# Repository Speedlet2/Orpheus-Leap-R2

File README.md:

# Orpheus-Leap-R2

This is the repository containing the current basic ideas for [Hack Club's](https://github.com/hackclub) new 'Orpheus Leap' uController board. The original version was designed by [Kevin Yang](https://github.com/kvnyng) in 2020 and can be found [here](https://github.com/kvnyng/Orpheus-Leap-Micro). This is currently very early in development, with the basic architecture not yet finalised. Feel free to add any ideas/problems in an issue

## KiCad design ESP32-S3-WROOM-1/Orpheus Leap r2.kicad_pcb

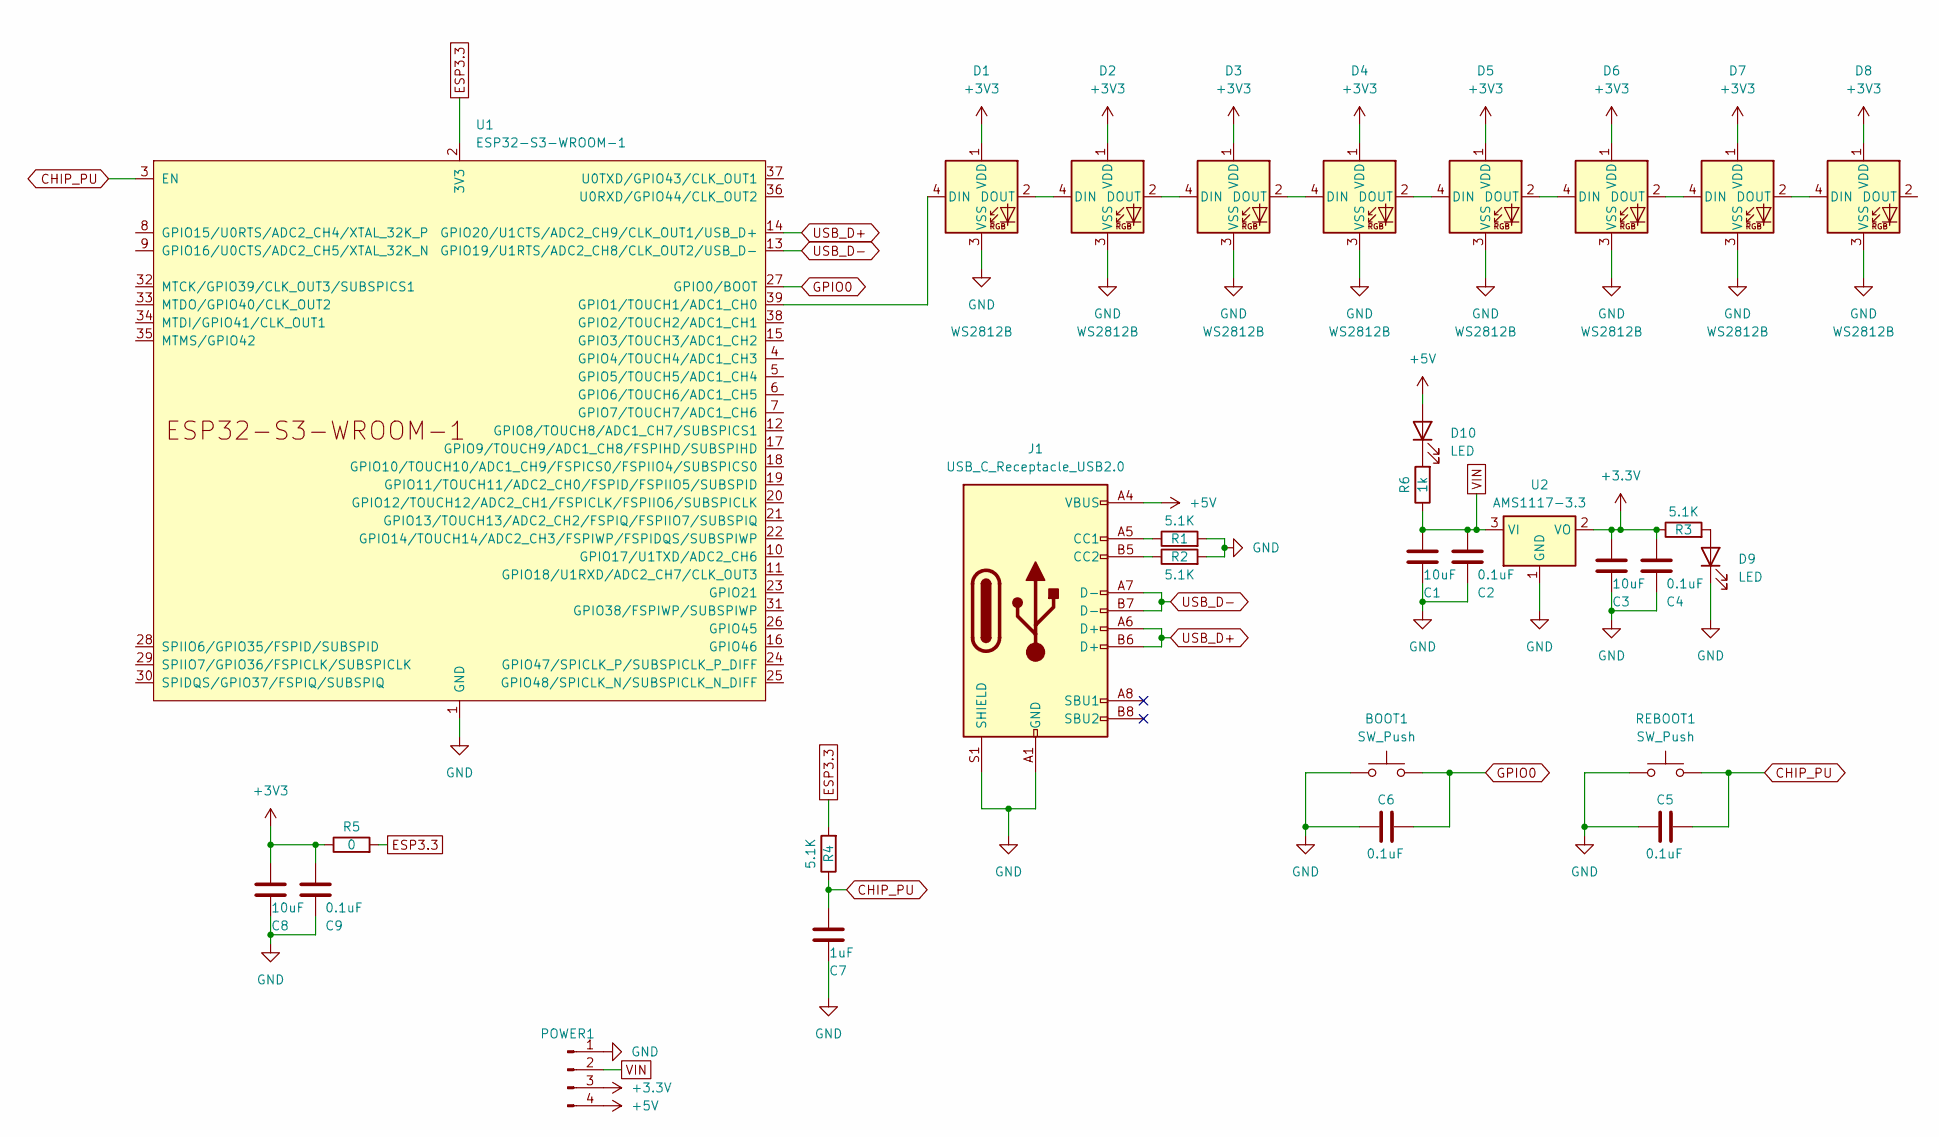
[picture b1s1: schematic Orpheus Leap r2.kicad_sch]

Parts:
BOOT1: SW_Push; SW_PUSH_6mm
C1, C3, C8: 10uF; C_0603_1608Metric
C2, C4, C5, C6, C9: 0.1uF; C_0603_1608Metric
C7: 1uF; C_0603_1608Metric
D1, D2, D3, D4, D5, D6, D7, D8: WS2812B; LED_WS2812B_PLCC4_5.0x5.0mm_P3.2mm
D9, D10: LED; LED_D3.0mm
J1: USB_C_Receptacle_USB2.0; USB_C_Receptacle_JAE_DX07S016JA1R1500
POWER1: Conn_01x04_Pin; PinHeader_1x04_P2.54mm_Vertical
R1, R2, R3, R4: 5.1K; R_0201_0603Metric
R5: 0; R_0201_0603Metric
R6: 1k; R_0201_0603Metric
REBOOT1: SW_Push; SW_PUSH_6mm
U1: ESP32-S3-WROOM-1
U2: AMS1117-3.3; SOT-223-3_TabPin2

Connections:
+3.3V: C3.1, C4.1, POWER1.3, R3.1, U2.2 (VO)
+3V3: C8.1, C9.1, D1.1 (VDD), D2.1 (VDD), D3.1 (VDD), D4.1 (VDD), D5.1 (VDD), D6.1 (VDD), D7.1 (VDD), D8.1 (VDD), R5.1
+5V: D10.2 (A), J1.A4 (VBUS), J1.A9 (VBUS), J1.B4 (VBUS), J1.B9 (VBUS), POWER1.4
CHIP_PU: C5.2, C7.1, R4.1, REBOOT1.2, U1.3 (EN)
ESP3.3: R4.2, R5.2, U1.2 (3V3)
GND: BOOT1.1, C1.2, C2.2, C3.2, C4.2, C5.1, C6.1, C7.2, C8.2, C9.2, D1.3 (VSS), D2.3 (VSS), D3.3 (VSS), D4.3 (VSS), D5.3 (VSS), D6.3 (VSS), D7.3 (VSS), D8.3 (VSS), D9.1 (K), J1.A1 (GND), J1.A12 (GND), J1.B1 (GND), J1.B12 (GND), J1.S1 (SHIELD), POWER1.1, R1.2, R2.2, REBOOT1.1, U1.1 (GND), U1.40 (GND), U1.41 (GND), U2.1 (GND)
GPIO0: BOOT1.2, C6.2, U1.27 (GPIO0/BOOT)
unnamed: D1.4 (DIN), U1.39 (GPIO1/TOUCH1/ADC1_CH0)
unnamed: D1.2 (DOUT), D2.4 (DIN)
unnamed: D2.2 (DOUT), D3.4 (DIN)
unnamed: D3.2 (DOUT), D4.4 (DIN)
unnamed: D4.2 (DOUT), D5.4 (DIN)
unnamed: D5.2 (DOUT), D6.4 (DIN)
unnamed: D6.2 (DOUT), D7.4 (DIN)
unnamed: D7.2 (DOUT), D8.4 (DIN)
unnamed: D9.2 (A), R3.2
unnamed: D10.1 (K), R6.2
unnamed: J1.A5 (CC1), R1.1
unnamed: J1.B5 (CC2), R2.1
USB_D+: J1.A6 (D+), J1.B6 (D+), U1.14 (GPIO20/U1CTS/ADC2_CH9/CLK_OUT1/USB_D+)
USB_D-: J1.A7 (D-), J1.B7 (D-), U1.13 (GPIO19/U1RTS/ADC2_CH8/CLK_OUT2/USB_D-)
VIN: C1.1, C2.1, POWER1.2, R6.1, U2.3 (VI)

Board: 2 copper layers, 31 parts (0 on the bottom side), 22 nets, no tracks yet.

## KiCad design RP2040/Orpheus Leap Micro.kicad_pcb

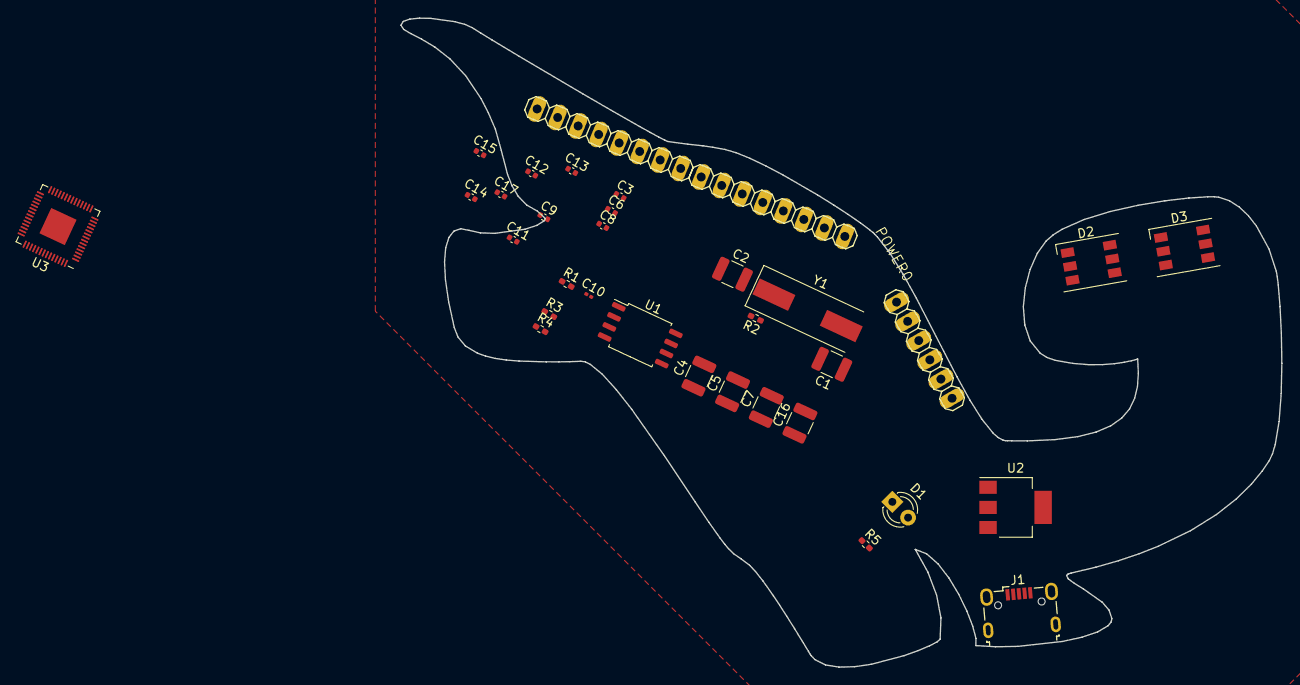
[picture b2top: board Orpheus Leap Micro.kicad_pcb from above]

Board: 2 copper layers, 100.8 x 74.2 mm, 33 parts (0 on the bottom side), 36 nets, no tracks yet.

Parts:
C1, C2, C4, C5, C7, C16: 10u; C_1210_3225Metric
C3, C6, C8, C9, C11, C12, C13, C14, C15, C17: 100n; C_0402_1005Metric
C10: 1u; C_0201_0603Metric
D1: LED; LED_D3.0mm_FlatTop
D2, D3: WS2813; LED_WS2812_PLCC6_5.0x5.0mm_P1.6mm
IOH0, IOH1: PINHD-1X8; 1X08
J1: USB_B_Micro; USB_Micro-B_Wuerth_629105150521
POWER0: PINHD-1X6; 1X06
R1, R2, R5: 1K; R_0402_1005Metric_Pad0.72x0.64mm_HandSolder
R3, R4: 27; R_0402_1005Metric_Pad0.72x0.64mm_HandSolder
U1: W25Q128JVS; SOIC-8_5.23x5.23mm_P1.27mm
U2: NCP1117-1.5_SOT223; SOT-223-3_TabPin2
U3: RP2040; QFN-56-1EP_7x7mm_P0.4mm_EP3.2x3.2mm
Y1: Crystal; Crystal_SMD_HC49-SD

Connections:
+1V1: C6.1, C7.1, C8.1, U3.23 (DVDD), U3.45 (VREG_VOUT), U3.50 (DVDD)
+3.3V: C3.1, C5.1, C9.1, C10.1, C11.1, C12.1, C13.1, C14.1, C15.1, C16.1, C17.1, D2.1 (VCC), D2.2 (VDD), D3.1 (VCC), D3.2 (VDD), POWER0.2, R1.2, U1.1 (~CS), U2.2 (VO), U3.1 (IOVDD), U3.10 (IOVDD), U3.22 (IOVDD), U3.33 (IOVDD), U3.42 (IOVDD), U3.43 (ADC_AVDD), U3.44 (VREG_IN), U3.48 (USB_VDD), U3.49 (IOVDD), U3.56 (QSPI_SS)
GND: D2.5 (GND), D3.5 (GND), POWER0.3, POWER0.4, POWER0.5, U1.4 (GND)
GPIO1: IOH0.1, U3.3 (GPIO1)
GPIO2: IOH0.2, U3.4 (GPIO2)
GPIO3: IOH0.3, U3.5 (GPIO3)
GPIO4: IOH0.4, U3.6 (GPIO4)
GPIO5: IOH0.5, U3.7 (GPIO5)
GPIO6: IOH0.6, U3.8 (GPIO6)
GPIO7: IOH0.7, U3.9 (GPIO7)
GPIO8: IOH0.8, U3.11 (GPIO8)
GPIO9: IOH1.1, U3.12 (GPIO9)
GPIO10: IOH1.2, U3.13 (GPIO10)
GPIO11: IOH1.3, U3.14 (GPIO11)
GPIO12: IOH1.4, U3.15 (GPIO12)
GPIO13: IOH1.5, U3.16 (GPIO13)
GPIO14: IOH1.6, U3.17 (GPIO14)
GPIO15: IOH1.7, U3.18 (GPIO15)
GPIO16: IOH1.8, U3.27 (GPIO16)
unnamed: C2.2, R2.1, Y1.1
unnamed: D1.2 (A), R5.2
unnamed: D2.4 (DIN), U3.2 (GPIO0)
unnamed: D2.3 (DOUT), D3.4 (DIN)
unnamed: C1.2, C2.1, C3.2, C4.2, C5.2, C6.2, C7.2, C8.2, C9.2, C10.2, C11.2, C12.2, C13.2, C14.2, C15.2, C16.2, C17.2, J1.5 (GND), J1.6 (Shield), U2.1 (GND), U3.57 (GND)
unnamed: U1.5 (DI(IO0)), U3.53 (QSPI_SD0)
unnamed: U1.2 (DO(IO1)), U3.55 (QSPI_SD1)
unnamed: U1.3 (IO2), U3.54 (QSPI_SD2)
unnamed: U1.7 (IO3), U3.51 (QSPI_SD3)
unnamed: R4.2, U3.46 (USB_DM)
unnamed: R3.2, U3.47 (USB_DP)
unnamed: C1.1, U3.20 (XIN), Y1.2
unnamed: R2.2, U3.21 (XOUT)
USB_D+: J1.3 (D+), R3.1
USB_D-: J1.2 (D-), R4.1
VBUS: J1.1 (VBUS), POWER0.1, R5.1
VCC: C4.1, D1.1 (K), POWER0.6, U2.3 (VI)
